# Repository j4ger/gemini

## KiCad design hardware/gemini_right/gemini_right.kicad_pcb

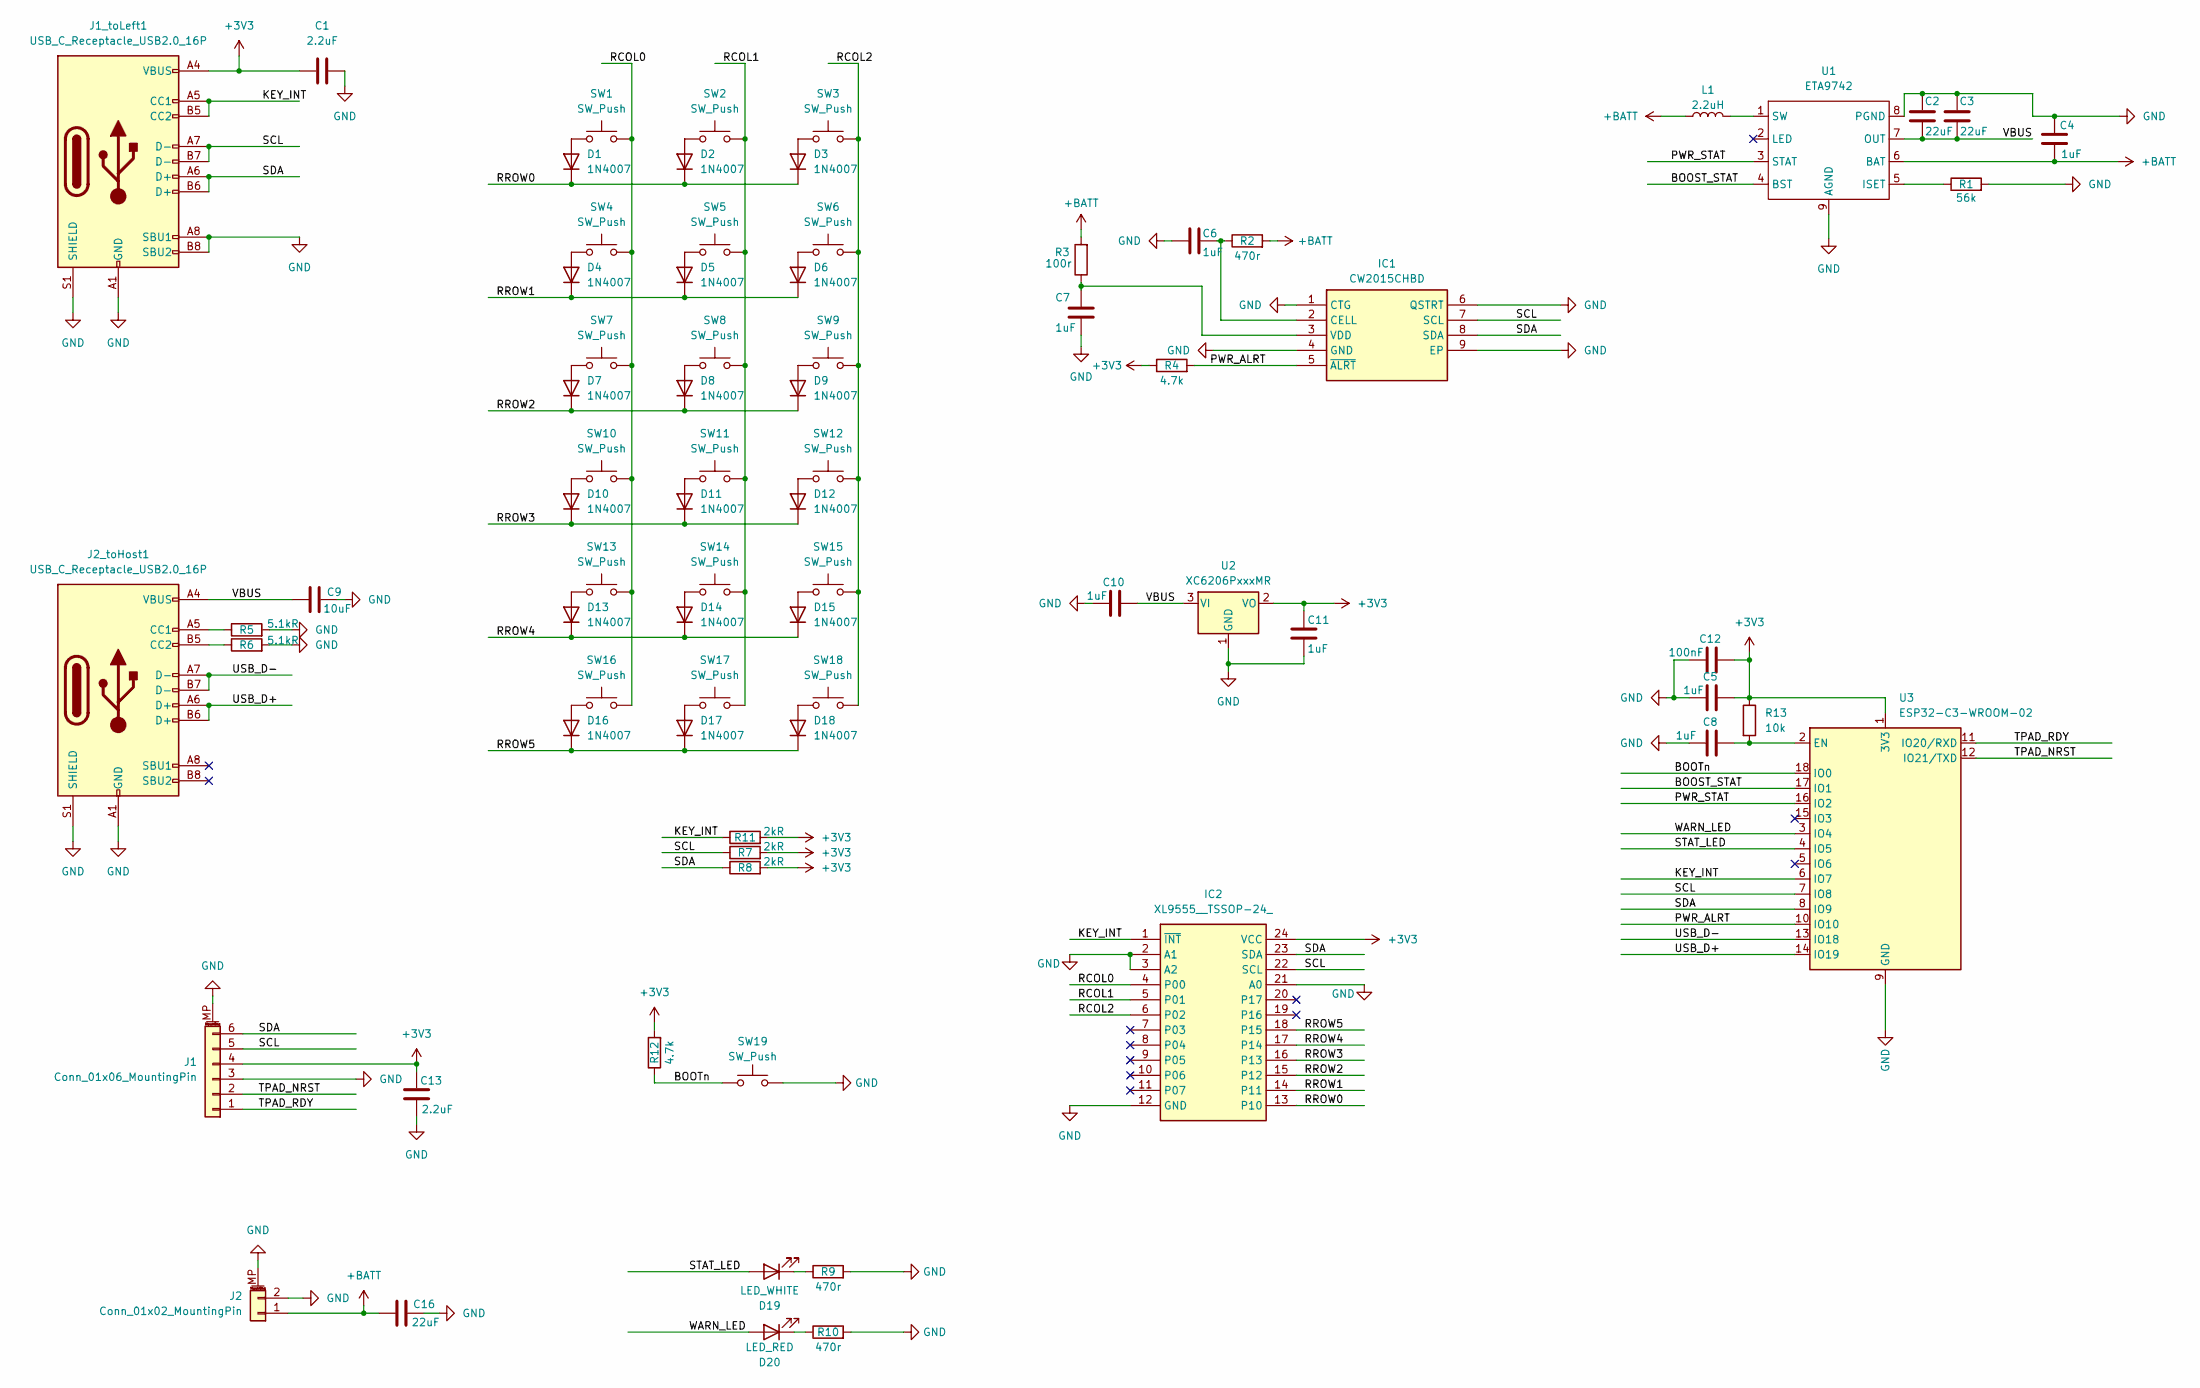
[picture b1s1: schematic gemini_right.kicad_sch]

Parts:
C1, C13: 2.2uF; C_0603_1608Metric_Pad1.08x0.95mm_HandSolder
C2, C3, C16: 22uF; C_0603_1608Metric_Pad1.08x0.95mm_HandSolder
C4, C5, C6, C7, C8, C10, C11: 1uF; C_0603_1608Metric_Pad1.08x0.95mm_HandSolder
C9: 10uF; C_0603_1608Metric_Pad1.08x0.95mm_HandSolder
C12: 100nF; C_0603_1608Metric_Pad1.08x0.95mm_HandSolder
D1, D2, D3, D4, D5, D6, D7, D8, D9, D10, D11, D12, D13, D14, D15, D16, D17, D18: 1N4007; D_SOD-123F
D19: LED_WHITE; LED_0603_1608Metric_Pad1.05x0.95mm_HandSolder
D20: LED_RED; LED_0603_1608Metric_Pad1.05x0.95mm_HandSolder
IC1: CW2015CHBD; TDFN-8-1EP_3x2mm_P0.5mm_EP1.4x1.4mm; Manufacturer_Part_Number CW2015CSAC
IC2: XL9555__TSSOP-24_; SOP65P640X120-24N; Manufacturer_Part_Number XL9555 (TSSOP-24)
J1: Conn_01x06_MountingPin; FPC-SMD_6P-P0.50_XUNPU_FPC-05F-6PH20
J1_toLeft1, J2_toHost1: USB_C_Receptacle_USB2.0_16P; USB_C_Receptacle_GCT_USB4105-xx-A_16P_TopMnt_Horizontal
J2: Conn_01x02_MountingPin; CONN-SMD_2P-P1.25_XUNPU_WAFER-MX1.25-2PWB
L1: 2.2uH; L_Chilisin_BMRA00040420
R1: 56k; R_0603_1608Metric_Pad0.98x0.95mm_HandSolder
R2, R9, R10: 470r; R_0603_1608Metric_Pad0.98x0.95mm_HandSolder
R3: 100r; R_0603_1608Metric_Pad0.98x0.95mm_HandSolder
R4, R12: 4.7k; R_0603_1608Metric_Pad0.98x0.95mm_HandSolder
R5, R6: 5.1kR; R_0603_1608Metric_Pad0.98x0.95mm_HandSolder
R7, R8, R11: 2kR; R_0603_1608Metric_Pad0.98x0.95mm_HandSolder
R13: 10k; R_0603_1608Metric_Pad0.98x0.95mm_HandSolder
SW1, SW2, SW3, SW4, SW5, SW6, SW7, SW8, SW9, SW10, SW11, SW12, SW13, SW14, SW15, SW16, SW17, SW18: SW_Push; SW_Kailh_Choc_V1V2_1.00u
SW19: SW_Push; SW_Tactile_SPST_NO_Straight_CK_PTS636Sx25SMTRLFS
U1: ETA9742; SOIC127P600X175-9N
U2: XC6206PxxxMR; SOT-23-3
U3: ESP32-C3-WROOM-02

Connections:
+3V3: C1.1, C5.2, C11.1, C12.2, C13.1, IC2.24 (VCC), J1.4, J1_toLeft1.A4 (VBUS), J1_toLeft1.A9 (VBUS), J1_toLeft1.B4 (VBUS), J1_toLeft1.B9 (VBUS), R4.1, R7.2, R8.2, R11.2, R12.2, R13.1, U2.2 (VO), U3.1 (3V3)
+BATT: C4.2, C16.1, J2.1, L1.1, R2.2, R3.2, U1.6 (BAT)
/BOOST_STAT: U1.4 (BST), U3.17 (IO1)
/BOOTn: R12.1, SW19.1, U3.18 (IO0)
/KEY_INT: IC2.1 (~INT), J1_toLeft1.A5 (CC1), J1_toLeft1.B5 (CC2), R11.1, U3.6 (IO7)
/PWR_ALRT: IC1.5 (~ALRT), R4.2, U3.10 (IO10)
/PWR_STAT: U1.3 (STAT), U3.16 (IO2)
/RCOL0: IC2.4 (P00), SW1.2, SW4.2, SW7.2, SW10.2, SW13.2, SW16.2
/RCOL1: IC2.5 (P01), SW2.2, SW5.2, SW8.2, SW11.2, SW14.2, SW17.2
/RCOL2: IC2.6 (P02), SW3.2, SW6.2, SW9.2, SW12.2, SW15.2, SW18.2
/RROW0: D1.1 (K), D2.1 (K), D3.1 (K), IC2.13 (P10)
/RROW1: D4.1 (K), D5.1 (K), D6.1 (K), IC2.14 (P11)
/RROW2: D7.1 (K), D8.1 (K), D9.1 (K), IC2.15 (P12)
/RROW3: D10.1 (K), D11.1 (K), D12.1 (K), IC2.16 (P13)
/RROW4: D13.1 (K), D14.1 (K), D15.1 (K), IC2.17 (P14)
/RROW5: D16.1 (K), D17.1 (K), D18.1 (K), IC2.18 (P15)
/SCL: IC1.7 (SCL), IC2.22 (SCL), J1.5, J1_toLeft1.A7 (D-), J1_toLeft1.B7 (D-), R7.1, U3.7 (IO8)
/SDA: IC1.8 (SDA), IC2.23 (SDA), J1.6, J1_toLeft1.A6 (D+), J1_toLeft1.B6 (D+), R8.1, U3.8 (IO9)
/STAT_LED: D19.2 (A), U3.4 (IO5)
/TPAD_NRST: J1.2, U3.12 (IO21/TXD)
/TPAD_RDY: J1.1, U3.11 (IO20/RXD)
/USB_D+: J2_toHost1.A6 (D+), J2_toHost1.B6 (D+), U3.14 (IO19)
/USB_D-: J2_toHost1.A7 (D-), J2_toHost1.B7 (D-), U3.13 (IO18)
/VBUS: C2.1, C3.1, C9.1, C10.2, J2_toHost1.A4 (VBUS), J2_toHost1.A9 (VBUS), J2_toHost1.B4 (VBUS), J2_toHost1.B9 (VBUS), U1.7 (OUT), U2.3 (VI)
/WARN_LED: D20.2 (A), U3.3 (IO4)
GND: C1.2, C2.2, C3.2, C4.1, C5.1, C6.2, C7.2, C8.1, C9.2, C10.1, C11.2, C12.1, C13.2, C16.2, IC1.1 (CTG), IC1.4 (GND), IC1.6 (QSTRT), IC1.9 (EP), IC2.2 (A1), IC2.3 (A2), IC2.12 (GND), IC2.21 (A0), J1.3, J1.MP (MountPin), J1_toLeft1.A1 (GND), J1_toLeft1.A8 (SBU1), J1_toLeft1.A12 (GND), J1_toLeft1.B1 (GND), J1_toLeft1.B8 (SBU2), J1_toLeft1.B12 (GND), J1_toLeft1.S1 (SHIELD), J2.2, J2.MP (MountPin), J2_toHost1.A1 (GND), J2_toHost1.A12 (GND), J2_toHost1.B1 (GND), J2_toHost1.B12 (GND), J2_toHost1.S1 (SHIELD), R1.2, R5.2, R6.2, R9.2, R10.2, SW19.2, U1.8 (PGND), U1.9 (AGND), U2.1 (GND), U3.9 (GND), U3.19 (GND)
unnamed: D1.2 (A), SW1.1
unnamed: D2.2 (A), SW2.1
unnamed: D3.2 (A), SW3.1
unnamed: D4.2 (A), SW4.1
unnamed: D5.2 (A), SW5.1
unnamed: D6.2 (A), SW6.1
unnamed: D7.2 (A), SW7.1
unnamed: D8.2 (A), SW8.1
unnamed: D9.2 (A), SW9.1
unnamed: D10.2 (A), SW10.1
unnamed: D11.2 (A), SW11.1
unnamed: D12.2 (A), SW12.1
unnamed: D13.2 (A), SW13.1
unnamed: D14.2 (A), SW14.1
unnamed: D15.2 (A), SW15.1
unnamed: D16.2 (A), SW16.1
unnamed: D17.2 (A), SW17.1
unnamed: D18.2 (A), SW18.1
unnamed: D19.1 (K), R9.1
unnamed: D20.1 (K), R10.1
unnamed: C6.1, IC1.2 (CELL), R2.1
unnamed: C7.1, IC1.3 (VDD), R3.1
unnamed: J2_toHost1.A5 (CC1), R5.1
unnamed: J2_toHost1.B5 (CC2), R6.1
unnamed: R1.1, U1.5 (ISET)
unnamed: L1.2, U1.1 (SW)
unnamed: C8.2, R13.2, U3.2 (EN)

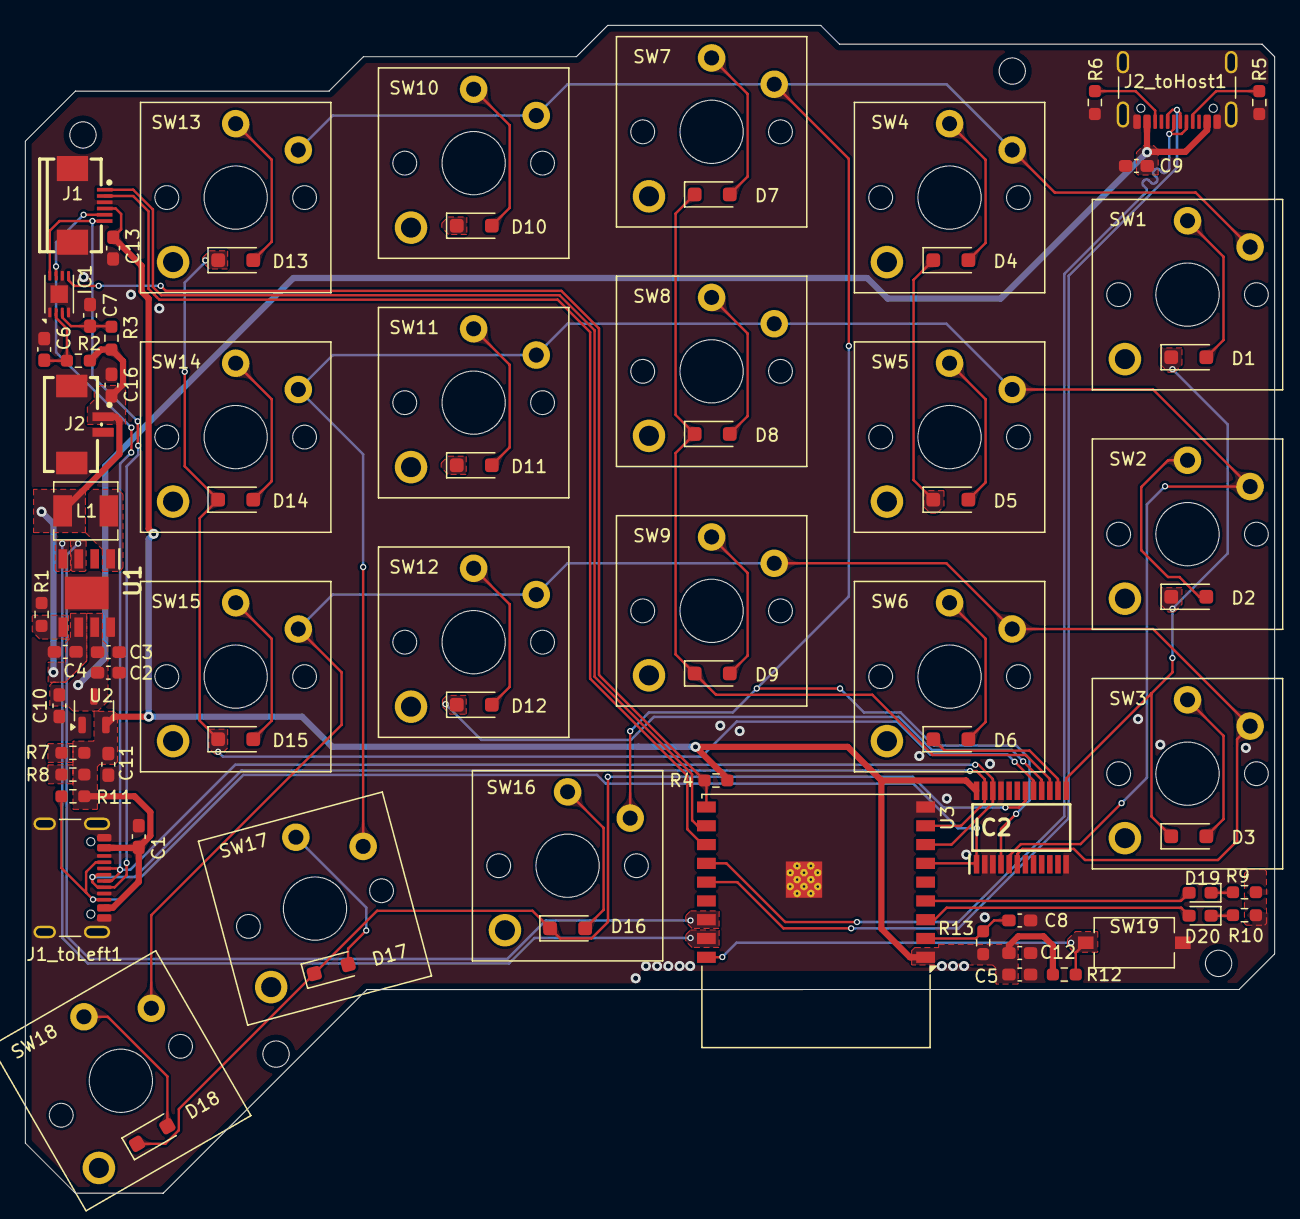
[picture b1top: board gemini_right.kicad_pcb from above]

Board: 2 copper layers, 99.8 x 93.2 mm, 76 parts (0 on the bottom side), 53 nets.

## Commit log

2023-04-04 Espnow latency test
2024-06-09 add kicad files & more tests
2024-06-09 cleanup
2024-06-13 initial routing for gemini_right
2024-06-14 test production 1
2024-06-15 routing of left side & cleanup
2024-06-17 add screw hole
2024-07-08 update schematics
2024-07-09 partially finish layout of new design
2024-07-10 update clearance & outline for left side
2024-07-11 finish routing for right half
2024-07-11 update routing for right half
2024-07-11 update capacitor
2024-08-14 use esp32c3 instead
2024-08-27 restructure
2024-08-27 init firmware
